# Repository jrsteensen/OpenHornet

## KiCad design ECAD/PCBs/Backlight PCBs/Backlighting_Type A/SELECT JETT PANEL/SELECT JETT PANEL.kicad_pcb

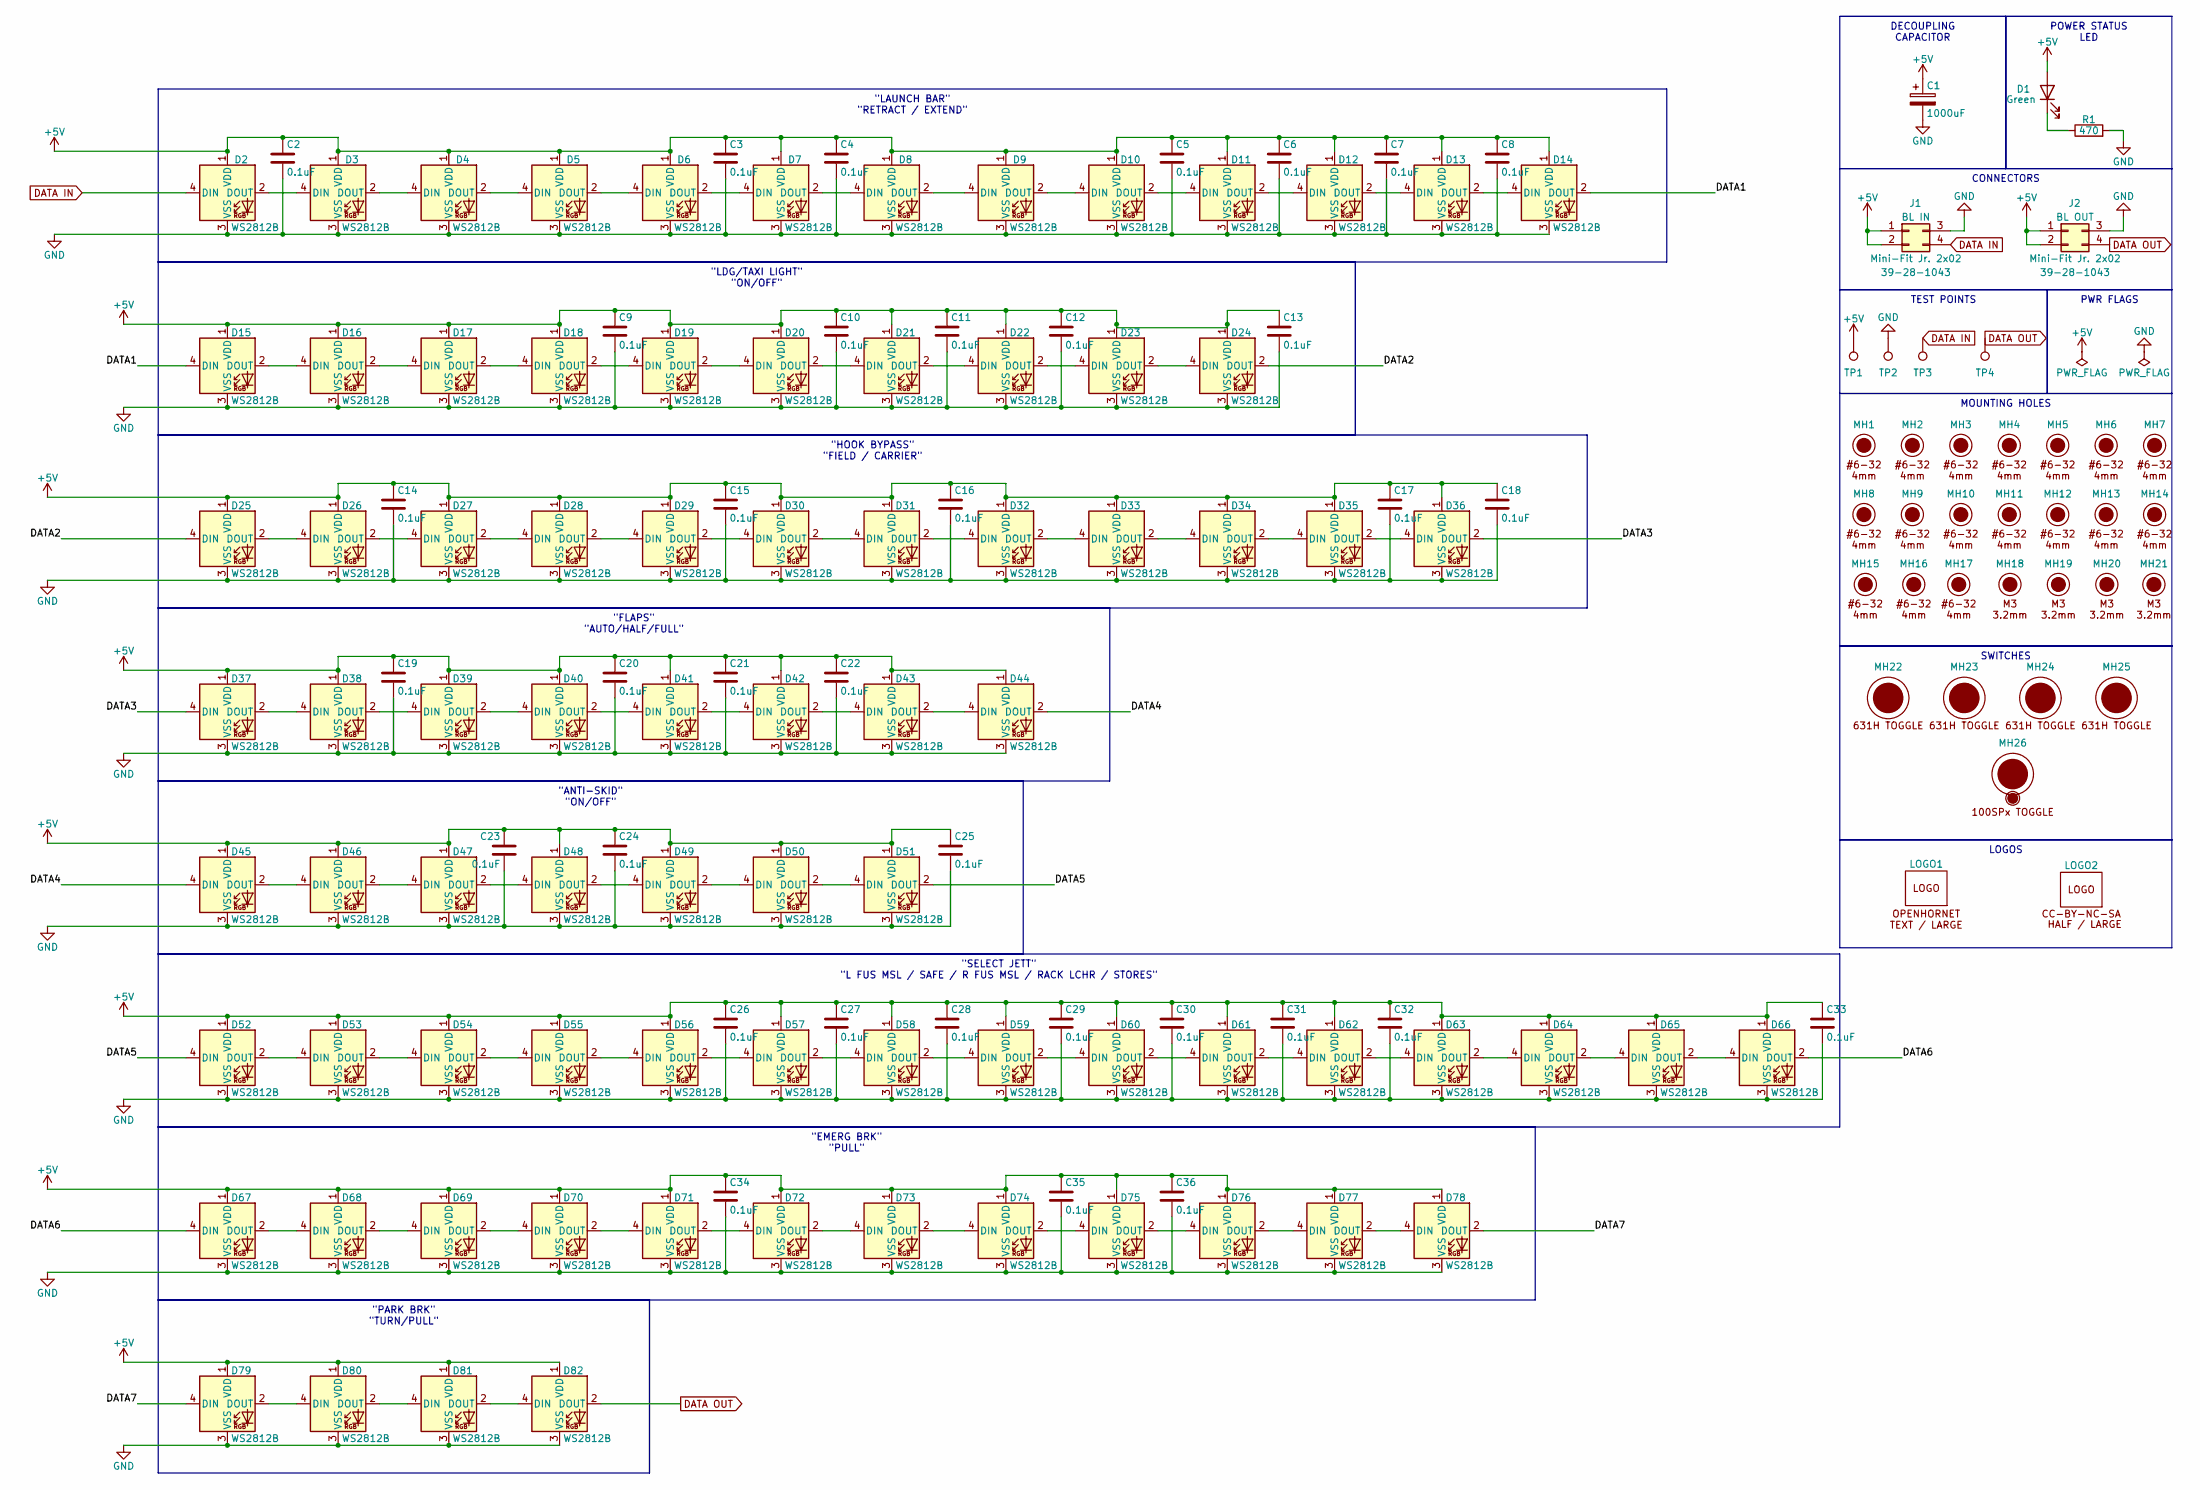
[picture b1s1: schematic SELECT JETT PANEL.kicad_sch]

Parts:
C1: 1000uF; CP_Elec_8x10; Manufacturer PN UWT0J102MNL1GS; LCSC C445083
C2, C3, C4, C5, C6, C7, C8, C9, C10, C11, C12, C13, C14, C15, C16, C17, C18, C19, C20, C21, C22, C23, C24, C25, C26, C27, C28, C29, C30, C31, C32, C33, C34, C35, C36: 0.1uF; C_0603_1608Metric; Manufacturer PN CC0603KRX7R9BB104; LCSC C14663
D1: Green; LED_D3.0mm; Manufacturer PN 151031VS06000
D2, D3, D4, D5, D6, D7, D8, D9, D10, D11, D12, D13, D14, D15, D16, D17, D18, D19, D20, D21, D22, D23, D24, D25, D26, D27, D28, D29, D30, D31, D32, D33, D34, D35, D36, D37, D38, D39, D40, D41, D42, D43, D44, D45, D46, D47, D48, D49, D50, D51, D52, D53, D54, D55, D56, D57, D58, D59, D60, D61, D62, D63, D64, D65, D66, D67, D68, D69, D70, D71, D72, D73, D74, D75, D76, D77, D78, D79, D80, D81, D82: WS2812B; LED_WS2812B_PLCC4_5.0x5.0mm_P3.2mm; Manufacturer PN WS2812B; LCSC C2761795
J1, J2: Mini-Fit Jr. 2x02; Molex_Mini-Fit_Jr_5566-04A_2x02_P4.20mm_Vertical; Manufacturer PN 39-28-1043; LCSC C293502
LOGO1: LOGO; LOGO_OH_Text_Large
LOGO2: LOGO; LOGO_CC-BY-NC-SA_Half_Large
MH1, MH2, MH3, MH4, MH5, MH6, MH7, MH8, MH9, MH10, MH11, MH12, MH13, MH14, MH15, MH16, MH17: 6x32 / 4mm; MountingHole_6-32_PHS
MH18, MH19, MH20, MH21: M3 / 3.2mm; MountingHole_3.2mm_M3_DIN965
MH22, MH23, MH24, MH25: Switch_631H; 631HX_Toggle_13mm_x_13mm; Manufacturer PN 631H
MH26: Switch_100SPx; 100SPX_Toggle_13mm_x_18mm
R1: 470; R_0603_1608Metric; Manufacturer PN 0603WAF4700T5E; LCSC C23179
TP1, TP2, TP3, TP4: TestPoint; TestPoint_THTPad_D1.5mm_Drill0.7mm

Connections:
+5V: C1.1, C2.1, C3.1, C4.1, C5.1, C6.1, C7.1, C8.1, C9.1, C10.1, C11.1, C12.1, C13.1, C14.1, C15.1, C16.1, C17.1, C18.1, C19.1, C20.1, C21.1, C22.1, C23.1, C24.1, C25.1, C26.1, C27.1, C28.1, C29.1, C30.1, C31.1, C32.1, C33.1, C34.1, C35.1, C36.1, D1.2 (A), D2.1 (VDD), D3.1 (VDD), D4.1 (VDD), D5.1 (VDD), D6.1 (VDD), D7.1 (VDD), D8.1 (VDD), D9.1 (VDD), D10.1 (VDD), D11.1 (VDD), D12.1 (VDD), D13.1 (VDD), D14.1 (VDD), D15.1 (VDD), D16.1 (VDD), D17.1 (VDD), D18.1 (VDD), D19.1 (VDD), D20.1 (VDD), D21.1 (VDD), D22.1 (VDD), D23.1 (VDD), D24.1 (VDD), D25.1 (VDD), D26.1 (VDD), D27.1 (VDD), D28.1 (VDD), D29.1 (VDD), D30.1 (VDD), D31.1 (VDD), D32.1 (VDD), D33.1 (VDD), D34.1 (VDD), D35.1 (VDD), D36.1 (VDD), D37.1 (VDD), D38.1 (VDD), D39.1 (VDD), D40.1 (VDD), D41.1 (VDD), D42.1 (VDD), D43.1 (VDD), D44.1 (VDD), D45.1 (VDD), D46.1 (VDD), D47.1 (VDD), D48.1 (VDD), D49.1 (VDD), D50.1 (VDD), D51.1 (VDD), D52.1 (VDD), D53.1 (VDD), D54.1 (VDD), D55.1 (VDD), D56.1 (VDD), D57.1 (VDD), D58.1 (VDD), D59.1 (VDD), D60.1 (VDD), D61.1 (VDD), D62.1 (VDD), D63.1 (VDD), D64.1 (VDD), D65.1 (VDD), D66.1 (VDD), D67.1 (VDD), D68.1 (VDD), D69.1 (VDD), D70.1 (VDD), D71.1 (VDD), D72.1 (VDD), D73.1 (VDD), D74.1 (VDD), D75.1 (VDD), D76.1 (VDD), D77.1 (VDD), D78.1 (VDD), D79.1 (VDD), D80.1 (VDD), D81.1 (VDD), D82.1 (VDD), J1.1, J1.2 (Pin_3), J2.1, J2.2 (Pin_3), TP1.1
/DATA1: D14.2 (DOUT), D15.4 (DIN)
/DATA2: D24.2 (DOUT), D25.4 (DIN)
/DATA3: D36.2 (DOUT), D37.4 (DIN)
/DATA4: D44.2 (DOUT), D45.4 (DIN)
/DATA5: D51.2 (DOUT), D52.4 (DIN)
/DATA6: D66.2 (DOUT), D67.4 (DIN)
/DATA7: D78.2 (DOUT), D79.4 (DIN)
DATA IN: D2.4 (DIN), J1.4, TP3.1
DATA OUT: D82.2 (DOUT), J2.4, TP4.1
GND: C1.2, C2.2, C3.2, C4.2, C5.2, C6.2, C7.2, C8.2, C9.2, C10.2, C11.2, C12.2, C13.2, C14.2, C15.2, C16.2, C17.2, C18.2, C19.2, C20.2, C21.2, C22.2, C23.2, C24.2, C25.2, C26.2, C27.2, C28.2, C29.2, C30.2, C31.2, C32.2, C33.2, C34.2, C35.2, C36.2, D2.3 (VSS), D3.3 (VSS), D4.3 (VSS), D5.3 (VSS), D6.3 (VSS), D7.3 (VSS), D8.3 (VSS), D9.3 (VSS), D10.3 (VSS), D11.3 (VSS), D12.3 (VSS), D13.3 (VSS), D14.3 (VSS), D15.3 (VSS), D16.3 (VSS), D17.3 (VSS), D18.3 (VSS), D19.3 (VSS), D20.3 (VSS), D21.3 (VSS), D22.3 (VSS), D23.3 (VSS), D24.3 (VSS), D25.3 (VSS), D26.3 (VSS), D27.3 (VSS), D28.3 (VSS), D29.3 (VSS), D30.3 (VSS), D31.3 (VSS), D32.3 (VSS), D33.3 (VSS), D34.3 (VSS), D35.3 (VSS), D36.3 (VSS), D37.3 (VSS), D38.3 (VSS), D39.3 (VSS), D40.3 (VSS), D41.3 (VSS), D42.3 (VSS), D43.3 (VSS), D44.3 (VSS), D45.3 (VSS), D46.3 (VSS), D47.3 (VSS), D48.3 (VSS), D49.3 (VSS), D50.3 (VSS), D51.3 (VSS), D52.3 (VSS), D53.3 (VSS), D54.3 (VSS), D55.3 (VSS), D56.3 (VSS), D57.3 (VSS), D58.3 (VSS), D59.3 (VSS), D60.3 (VSS), D61.3 (VSS), D62.3 (VSS), D63.3 (VSS), D64.3 (VSS), D65.3 (VSS), D66.3 (VSS), D67.3 (VSS), D68.3 (VSS), D69.3 (VSS), D70.3 (VSS), D71.3 (VSS), D72.3 (VSS), D73.3 (VSS), D74.3 (VSS), D75.3 (VSS), D76.3 (VSS), D77.3 (VSS), D78.3 (VSS), D79.3 (VSS), D80.3 (VSS), D81.3 (VSS), D82.3 (VSS), J1.3 (Pin_2), J2.3 (Pin_2), R1.2, TP2.1
unnamed: D1.1 (K), R1.1
unnamed: D2.2 (DOUT), D3.4 (DIN)
unnamed: D3.2 (DOUT), D4.4 (DIN)
unnamed: D4.2 (DOUT), D5.4 (DIN)
unnamed: D5.2 (DOUT), D6.4 (DIN)
unnamed: D6.2 (DOUT), D7.4 (DIN)
unnamed: D7.2 (DOUT), D8.4 (DIN)
unnamed: D8.2 (DOUT), D9.4 (DIN)
unnamed: D9.2 (DOUT), D10.4 (DIN)
unnamed: D10.2 (DOUT), D11.4 (DIN)
unnamed: D11.2 (DOUT), D12.4 (DIN)
unnamed: D12.2 (DOUT), D13.4 (DIN)
unnamed: D13.2 (DOUT), D14.4 (DIN)
unnamed: D15.2 (DOUT), D16.4 (DIN)
unnamed: D16.2 (DOUT), D17.4 (DIN)
unnamed: D17.2 (DOUT), D18.4 (DIN)
unnamed: D18.2 (DOUT), D19.4 (DIN)
unnamed: D19.2 (DOUT), D20.4 (DIN)
unnamed: D20.2 (DOUT), D21.4 (DIN)
unnamed: D21.2 (DOUT), D22.4 (DIN)
unnamed: D22.2 (DOUT), D23.4 (DIN)
unnamed: D23.2 (DOUT), D24.4 (DIN)
unnamed: D25.2 (DOUT), D26.4 (DIN)
unnamed: D26.2 (DOUT), D27.4 (DIN)
unnamed: D27.2 (DOUT), D28.4 (DIN)
unnamed: D28.2 (DOUT), D29.4 (DIN)
unnamed: D29.2 (DOUT), D30.4 (DIN)
unnamed: D30.2 (DOUT), D31.4 (DIN)
unnamed: D31.2 (DOUT), D32.4 (DIN)
unnamed: D32.2 (DOUT), D33.4 (DIN)
unnamed: D33.2 (DOUT), D34.4 (DIN)
unnamed: D34.2 (DOUT), D35.4 (DIN)
unnamed: D35.2 (DOUT), D36.4 (DIN)
unnamed: D37.2 (DOUT), D38.4 (DIN)
unnamed: D38.2 (DOUT), D39.4 (DIN)
unnamed: D39.2 (DOUT), D40.4 (DIN)
unnamed: D40.2 (DOUT), D41.4 (DIN)
unnamed: D41.2 (DOUT), D42.4 (DIN)
unnamed: D42.2 (DOUT), D43.4 (DIN)
unnamed: D43.2 (DOUT), D44.4 (DIN)
unnamed: D45.2 (DOUT), D46.4 (DIN)
unnamed: D46.2 (DOUT), D47.4 (DIN)
unnamed: D47.2 (DOUT), D48.4 (DIN)
unnamed: D48.2 (DOUT), D49.4 (DIN)
unnamed: D49.2 (DOUT), D50.4 (DIN)
unnamed: D50.2 (DOUT), D51.4 (DIN)
unnamed: D52.2 (DOUT), D53.4 (DIN)
unnamed: D53.2 (DOUT), D54.4 (DIN)
unnamed: D54.2 (DOUT), D55.4 (DIN)
unnamed: D55.2 (DOUT), D56.4 (DIN)
unnamed: D56.2 (DOUT), D57.4 (DIN)
unnamed: D57.2 (DOUT), D58.4 (DIN)
unnamed: D58.2 (DOUT), D59.4 (DIN)
unnamed: D59.2 (DOUT), D60.4 (DIN)
unnamed: D60.2 (DOUT), D61.4 (DIN)
unnamed: D61.2 (DOUT), D62.4 (DIN)
unnamed: D62.2 (DOUT), D63.4 (DIN)
unnamed: D63.2 (DOUT), D64.4 (DIN)
unnamed: D64.2 (DOUT), D65.4 (DIN)
unnamed: D65.2 (DOUT), D66.4 (DIN)
unnamed: D67.2 (DOUT), D68.4 (DIN)
unnamed: D68.2 (DOUT), D69.4 (DIN)
unnamed: D69.2 (DOUT), D70.4 (DIN)
unnamed: D70.2 (DOUT), D71.4 (DIN)
unnamed: D71.2 (DOUT), D72.4 (DIN)
unnamed: D72.2 (DOUT), D73.4 (DIN)
unnamed: D73.2 (DOUT), D74.4 (DIN)
unnamed: D74.2 (DOUT), D75.4 (DIN)
unnamed: D75.2 (DOUT), D76.4 (DIN)
unnamed: D76.2 (DOUT), D77.4 (DIN)
unnamed: D77.2 (DOUT), D78.4 (DIN)
unnamed: D79.2 (DOUT), D80.4 (DIN)
unnamed: D80.2 (DOUT), D81.4 (DIN)
unnamed: D81.2 (DOUT), D82.4 (DIN)

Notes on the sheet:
PWR FLAGS
LOGOS
"FLAPS" "AUTO/HALF/FULL"
POWER STATUS LED
"EMERG BRK" "PULL"
"ANTI-SKID" "ON/OFF"
CONNECTORS
"LDG/TAXI LIGHT" "ON/OFF"
"SELECT JETT" "L FUS MSL / SAFE / R FUS MSL / RACK LCHR / STORES"
"PARK BRK" "TURN/PULL"
DECOUPLING CAPACITOR
"LAUNCH BAR" "RETRACT / EXTEND"
SWITCHES
"HOOK BYPASS" "FIELD / CARRIER"
MOUNTING HOLES
TEST POINTS

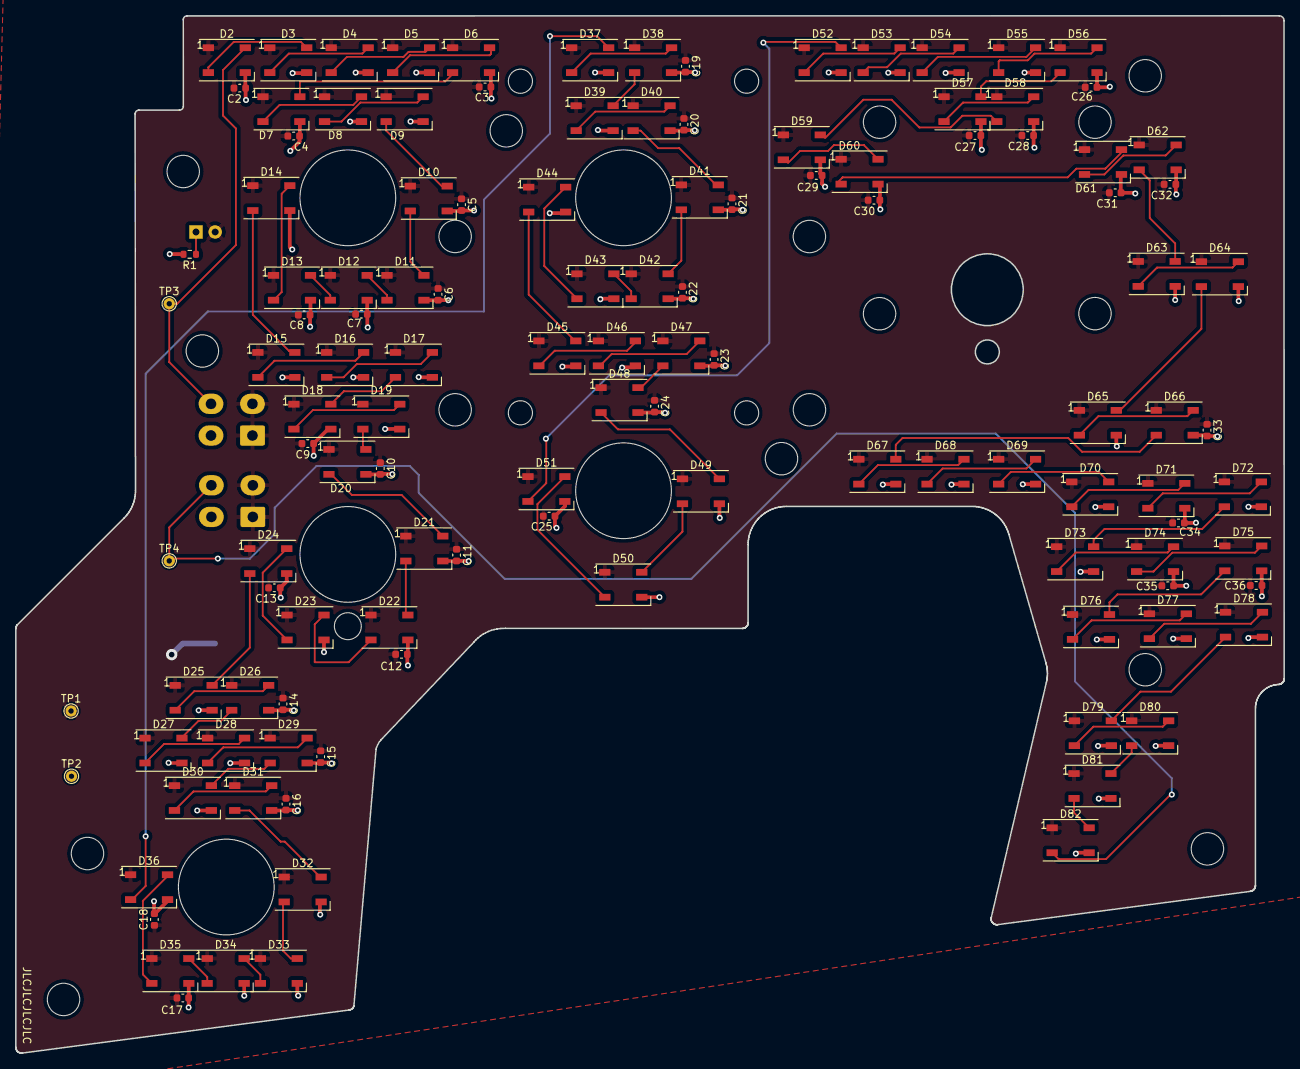
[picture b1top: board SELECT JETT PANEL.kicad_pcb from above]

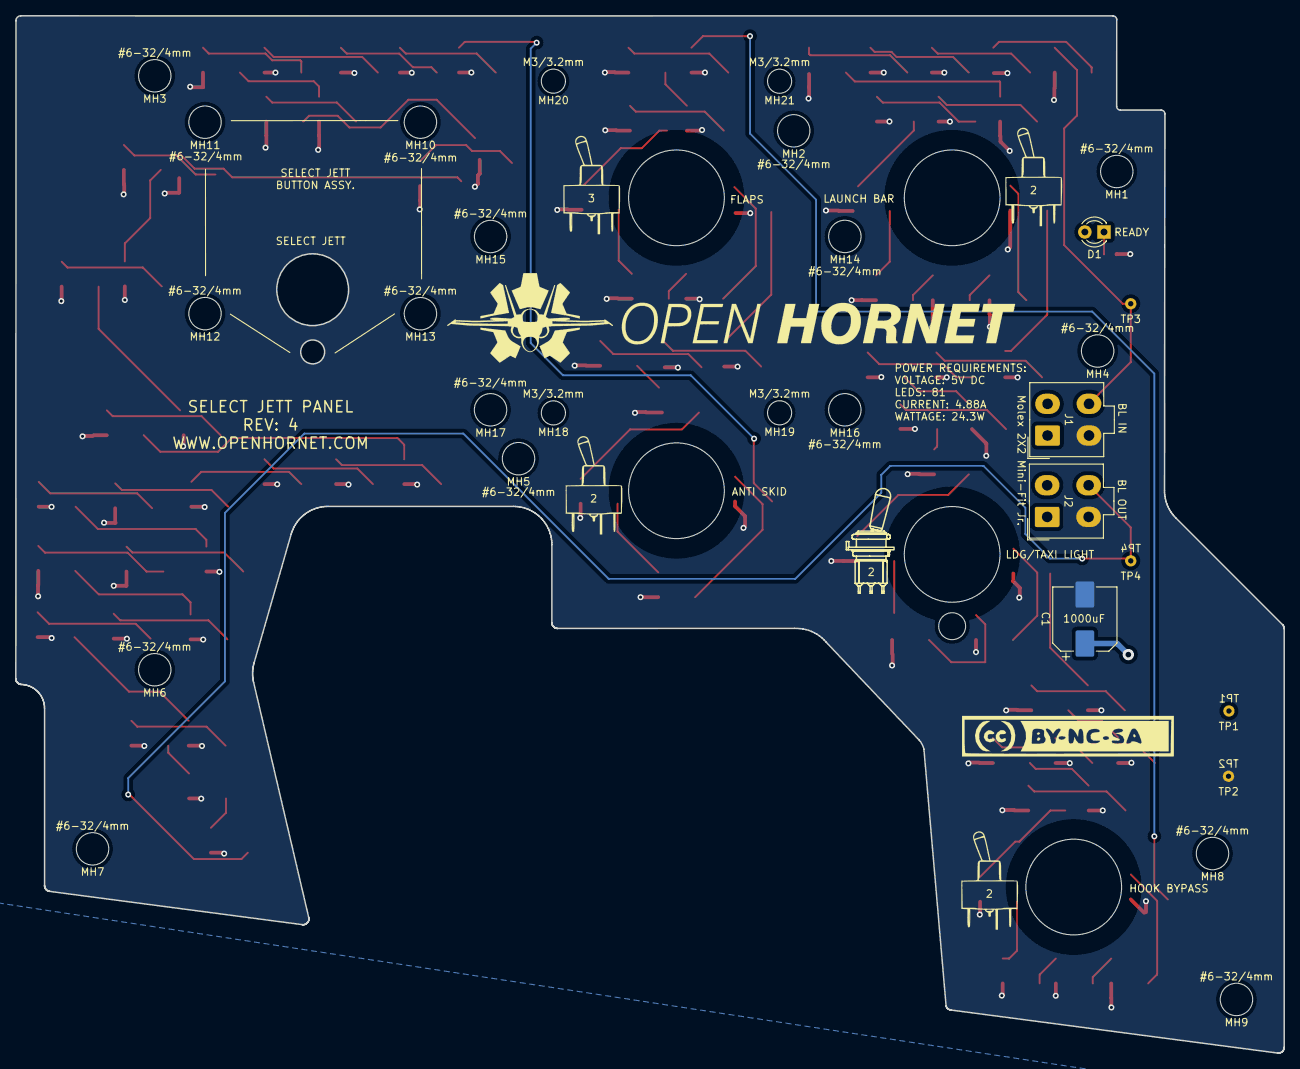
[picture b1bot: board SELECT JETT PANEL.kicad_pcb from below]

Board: 2 copper layers, 168.3 x 137.6 mm, 158 parts (32 on the bottom side), 85 nets.

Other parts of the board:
LOGO3, LOGO5, LOGO6: LOGO; 631H2_Toggle_Silkscreen
LOGO4: LOGO; 631H3_Toggle_Silkscreen
LOGO7: LOGO; 100SP1_Toggle_Silkscreen

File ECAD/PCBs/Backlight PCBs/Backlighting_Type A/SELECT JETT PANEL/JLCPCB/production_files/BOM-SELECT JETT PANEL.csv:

Comment,Designator,Footprint,LCSC
0.1uF,"C10,C11,C12,C13,C14,C15,C16,C17,C18,C19,C2,C20,C21,C22,C23,C24,C25,C26,C27,C28,C29,C3,C30,C31,C32,C33,C34,C35,C36,C4,C5,C6,C7,C8,C9",C_0603_1608Metric,C14663
470,R1,R_0603_1608Metric,C23179
WS2812B,"D10,D11,D12,D13,D14,D15,D16,D17,D18,D19,D2,D20,D21,D22,D23,D24,D25,D26,D27,D28,D29,D3,D30,D31,D32,D33,D34,D35,D36,D37,D38,D39,D4,D40,D41,D42,D43,D44,D45,D46,D47,D48,D49,D5,D50,D51,D52,D53,D54,D55,D56,D57,D58,D59,D6,D60,D61,D62,D63,D64,D65,D66,D67,D68,D69,D7,D70,D71,D72,D73,D74,D75,D76,D77,D78,D79,D8,D80,D81,D82,D9",LED_WS2812B_PLCC4_5.0x5.0mm_P3.2mm,C2761795
Mini-Fit Jr. 2x02,"J1,J2",Molex_Mini-Fit_Jr_5566-04A_2x02_P4.20mm_Vertical,C293502
1000uF,C1,CP_Elec_8x10,C445083
Green,D1,LED_D3.0mm,

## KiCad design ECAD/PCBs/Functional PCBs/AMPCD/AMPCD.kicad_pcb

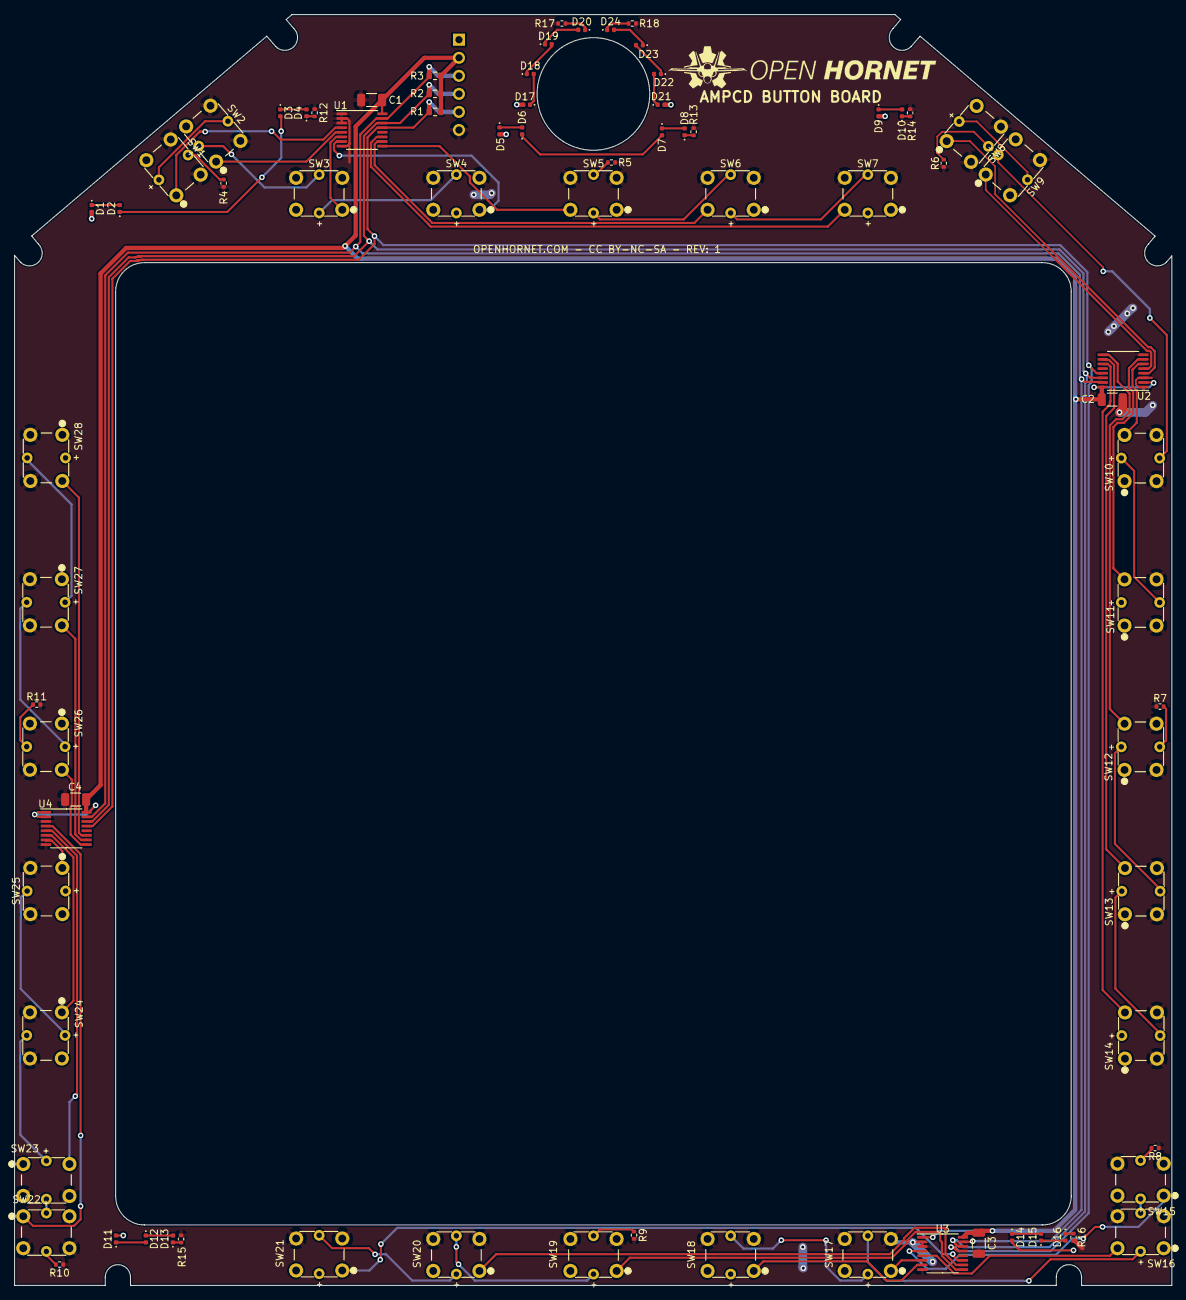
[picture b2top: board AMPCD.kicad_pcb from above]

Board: 2 copper layers, 162.9 x 178.9 mm, 79 parts (1 on the bottom side), 72 nets.

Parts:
C1, C2, C3, C4: 47uF; C_1206_3216Metric
D1, D2, D3, D4, D5, D6, D7, D8, D9, D10, D11, D12, D13, D14, D15, D16, D17, D18, D19, D20, D21, D22, D23, D24: LED; LED_0402_1005Metric
J1: Conn_01x06; PinHeader_1x06_P2.54mm_Horizontal
R1, R2, R3: 10K; R_0603_1608Metric
R4, R6, R8, R10, R12, R13, R17, R18: 33; R_0402_1005Metric
R5, R7, R9, R11, R15, R16: 150; R_0402_1005Metric
R14: 270; R_0402_1005Metric
SW1, SW2, SW3, SW4, SW5, SW6, SW7, SW8, SW9, SW10, SW11, SW12, SW13, SW14, SW15, SW16, SW17, SW18, SW19, SW20, SW21, SW22, SW23, SW24, SW25, SW26, SW27, SW28: TL1240GQ_old
U1, U2, U3, U4: TCA9554PWR; TSSOP-16_4.4x5mm_P0.65mm

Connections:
+5V: C1.1, C2.1, C3.1, C4.1, J1.2, R1.1, R2.1, R3.1, U1.16, U2.2, U2.16, U3.1, U3.16, U4.1, U4.2, U4.16
/U1P3: SW4.1, U1.7
/U1P4: SW5.1, U1.9
/U1P5: SW6.1, U1.10
/U1P6: SW7.1, U1.11
/U2P0: SW8.1, U2.4
/U2P1: SW9.1, U2.5
/U2P4: SW12.1, U2.9
/U2P5: SW13.1, U2.10
/U2P6: SW14.1, U2.11
/U3P4: SW19.1, U3.9
/U3P5: SW20.1, U3.10
/U3P6: SW21.1, U3.11
/U4P0: SW22.1, U4.4
/U4P1: SW23.1, U4.5
GND: C1.2, C2.2, C3.2, C4.2, J1.6, R4.1, R5.1, R6.1, R7.1, R8.1, R9.1, R10.1, R11.1, R12.2, R13.2, R14.2, R15.2, R16.2, R17.2, R18.2, SW1.2, SW2.2, SW3.2, SW4.2, SW5.2, SW6.2, SW7.2, SW8.2, SW9.2, SW10.2, SW11.2, SW12.2, SW13.2, SW14.2, SW15.2, SW16.2, SW17.2, SW18.2, SW19.2, SW20.2, SW21.2, SW22.2, SW23.2, SW24.2, SW25.2, SW26.2, SW27.2, SW28.2, U1.1, U1.2, U1.3, U1.8, U2.1, U2.3, U2.8, U3.2, U3.3, U3.8, U4.3, U4.8
IRQ: J1.5, R1.2, U1.13, U2.13, U3.13, U4.13
unnamed: D1.1, D2.2
unnamed: D2.1, D3.2
unnamed: D3.1, D4.2
unnamed: D4.1, R12.1
unnamed: D5.1, D6.2
unnamed: D6.1, D7.2
unnamed: D7.1, D8.2
unnamed: D8.1, R13.1
unnamed: D10.1, R14.1
unnamed: D9.1, D10.2
unnamed: D11.1, D12.2
unnamed: D12.1, D13.2
unnamed: D13.1, R15.1
unnamed: D14.1, D15.2
unnamed: D15.1, D16.2
unnamed: D16.1, R16.1
unnamed: D17.1, D18.2
unnamed: D18.1, D19.2
unnamed: D19.1, D20.2
unnamed: D20.1, R17.1
unnamed: D21.1, D22.2
unnamed: D22.1, D23.2
unnamed: D23.1, D24.2
unnamed: D24.1, R18.1
unnamed: R4.2, SW1.3
unnamed: R5.2, SW5.3
unnamed: R6.2, SW8.3
unnamed: R7.2, SW12.3
unnamed: R8.2, SW15.3
unnamed: R9.2, SW19.3
unnamed: R10.2, SW22.3
unnamed: R11.2, SW26.3
unnamed: SW1.4, SW2.3
unnamed: SW2.4, SW3.3
unnamed: SW3.4, SW4.3
unnamed: SW5.4, SW6.3
unnamed: SW6.4, SW7.3
unnamed: SW8.4, SW9.3
unnamed: SW9.4, SW10.3
unnamed: SW10.4, SW11.3
unnamed: SW12.4, SW13.3
unnamed: SW13.4, SW14.3
unnamed: SW15.4, SW16.3
unnamed: SW16.4, SW17.3
unnamed: SW17.4, SW18.3
unnamed: SW19.4, SW20.3
unnamed: SW20.4, SW21.3
unnamed: SW22.4, SW23.3
unnamed: SW23.4, SW24.3
unnamed: SW24.4, SW25.3
unnamed: SW26.4, SW27.3
unnamed: SW27.4, SW28.3
SCL: J1.4, R2.2, U1.14, U2.14, U3.14, U4.14
SDA: J1.3, R3.2, U1.15, U2.15, U3.15, U4.15
VCC: D1.2, D5.2, D9.2, D11.2, D14.2, D17.2, D21.2, J1.1, SW4.4, SW7.4, SW11.4, SW14.4, SW18.4, SW21.4, SW25.4, SW28.4

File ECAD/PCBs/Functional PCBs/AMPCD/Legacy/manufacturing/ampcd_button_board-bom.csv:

Comment,Designator,Footprint,LCSC
"47uF","C1,C2,C3,C4","Capacitor_SMD:C_1206_3216Metric","C96123"
"LED","D1,D2,D3,D4,D5,D6,D7,D8,D9,D10,D11,D12,D13,D14,D15,D16,D17,D18,D19,D20,D21,D22,D23,D24","LED_SMD:LED_0402_1005Metric","C130723"
"Conn_01x06","J1","Connector_PinHeader_2.54mm:PinHeader_1x06_P2.54mm_Horizontal",""
"33","R4,R6,R8,R10,R12,R13,R17,R18","Resistor_SMD:R_0402_1005Metric","C25105"
"270","R14","Resistor_SMD:R_0402_1005Metric","C25099"
"150","R5,R7,R9,R11,R15,R16","Resistor_SMD:R_0402_1005Metric","C25082"
"10K","R1,R2,R3","Resistor_SMD:R_0603_1608Metric","C25804"
"TL1240GQ","SW1,SW2,SW3,SW4,SW5,SW6,SW7,SW8,SW9,SW10,SW11,SW12,SW13,SW14,SW15,SW16,SW17,SW18,SW19,SW20,SW21,SW22,SW23,SW24,SW25,SW26,SW27,SW28","KiCAD Libraries:TL1240GQ",""
"TCA9554PWR","U1,U2,U3,U4","Package_SO:TSSOP-16_4.4x5mm_P0.65mm","C477924"

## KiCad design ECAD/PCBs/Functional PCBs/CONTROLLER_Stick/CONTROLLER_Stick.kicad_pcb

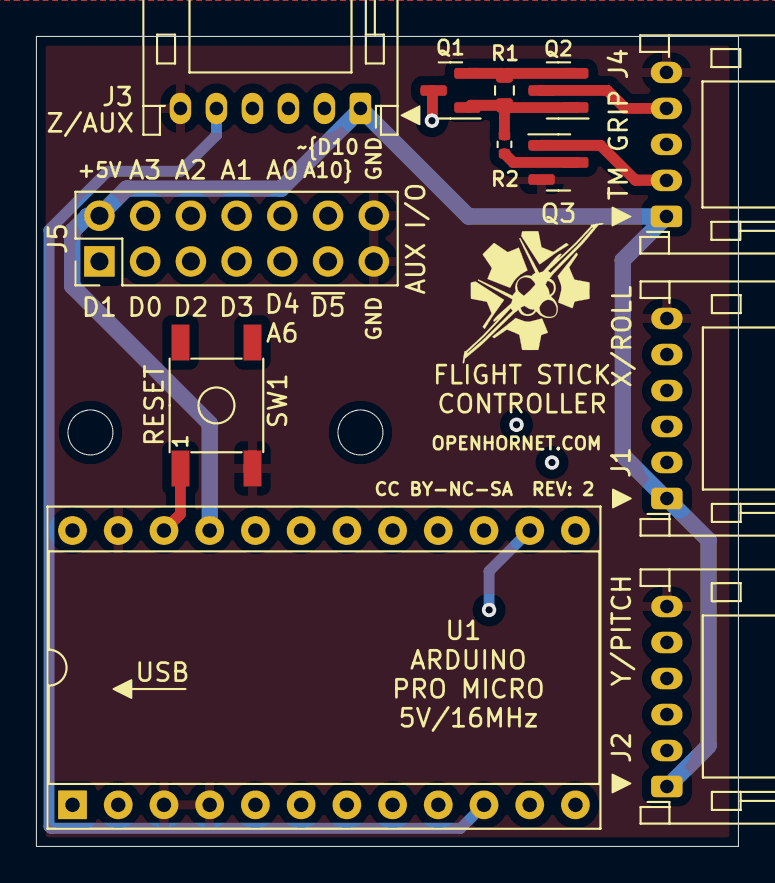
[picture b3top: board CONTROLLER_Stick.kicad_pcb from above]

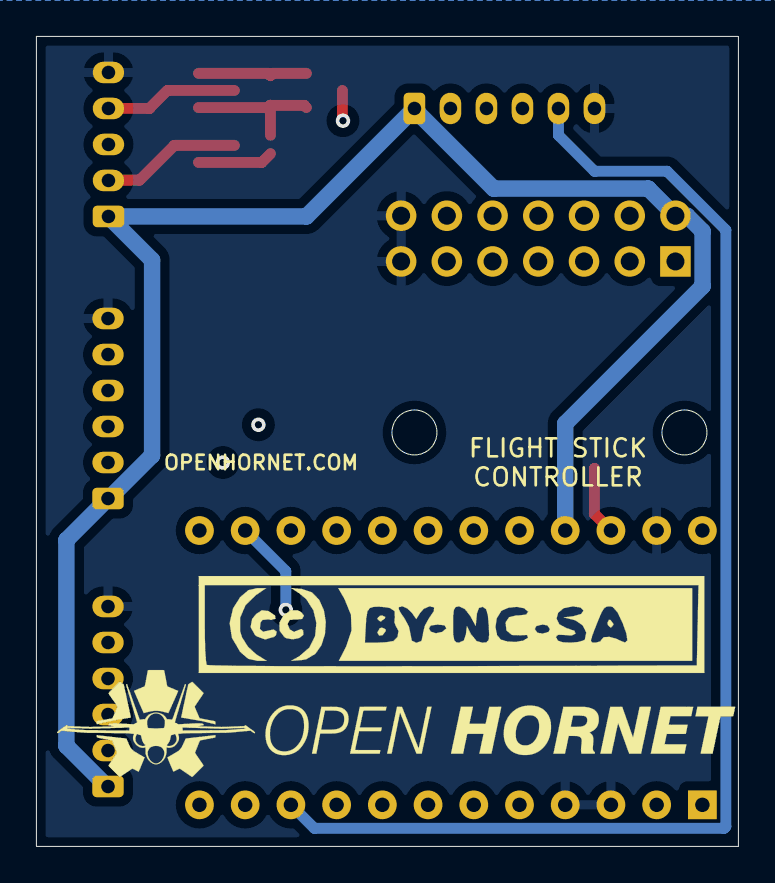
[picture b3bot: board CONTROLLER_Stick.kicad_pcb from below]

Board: 4 copper layers, 39.0 x 45.0 mm, 17 parts (2 on the bottom side), 25 nets.

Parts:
H1, H2: MountingHole; MountingHole_2.5mm
J1: X/ROLL; JST_PH_S6B-PH-K_1x06_P2.00mm_Horizontal
J2: Y/PITCH; JST_PH_S6B-PH-K_1x06_P2.00mm_Horizontal
J3: Z/AUX; JST_PH_S6B-PH-K_1x06_P2.00mm_Horizontal
J4: TM GRIP; JST_PH_S5B-PH-K_1x05_P2.00mm_Horizontal
J5: AUX I/O; PinHeader_2x07_P2.54mm_Vertical
LOGO1: OpenHornetLogoSmall; OH_LOGO_37.7mm_5.9mm
LOGO2: OpenHornetLogoSmall; CC-BY-NC-SA-Small
LOGO3: OpenHornetLogoSmall; OH_LOGO_ONLY_11x6mm
Q1, Q2: IRLML6402TRPBF; SOT-23
Q3: 2N7002; SOT-23
R1: 10k; R_0603_1608Metric
R2: 33; R_0402_1005Metric
SW1: RESET; SMD-SW-4_5.1x5.1
U1: ProMicro; DIP-24_W15.24mm_Socket

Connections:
+5V: J1.1, J2.1, J3.1, J4.1, J5.2, U1.21
/A0: J5.10, U1.17
/A1: J5.8, U1.18
/A2: J5.6, U1.19
/A3: J5.4, U1.20
/CSg: J4.2, Q3.1, U1.9
/CSx: J1.5, U1.12
/CSy: J2.5, U1.11
/CSz: J3.5, U1.10
/D0: J5.3, U1.2
/D1: J5.1, U1.1
/D2: J5.5, U1.5
/D4A6: J5.9, U1.7
/MISO: J1.2, J2.2, J3.2, Q1.3, U1.15
/MISOg: J4.4, Q2.3
/MOSI: J1.3, J2.3, J3.3, U1.14
/RST: SW1.1, U1.22
/SCK: J1.4, J2.4, J3.4, J4.3, U1.16
/~D3: J5.7, U1.6
/~D5: J5.11, U1.8
/~D10A10: J5.12, U1.13
GND: J1.6, J2.6, J3.6, J4.5, J5.13, J5.14, Q3.2, SW1.3, U1.3, U1.4, U1.23
unnamed: Q1.1, Q2.1, R1.2, R2.1
unnamed: Q1.2, Q2.2, R1.1
unnamed: Q3.3, R2.2

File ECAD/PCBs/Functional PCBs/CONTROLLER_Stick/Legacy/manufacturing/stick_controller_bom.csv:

Comment,Designator,Footprint,LCSC
"MountingHole","H1,H2","MountingHole:MountingHole_2.5mm",""
"X/ROLL","J1","Connector_JST:JST_PH_S6B-PH-K_1x06_P2.00mm_Horizontal","C265105"
"Y/PITCH","J2","Connector_JST:JST_PH_S6B-PH-K_1x06_P2.00mm_Horizontal","C265105"
"Z/AUX","J3","Connector_JST:JST_PH_S6B-PH-K_1x06_P2.00mm_Horizontal","C265105"
"TM GRIP","J4","Connector_JST:JST_PH_S5B-PH-K_1x05_P2.00mm_Horizontal","C157923"
"AUX I/O","J5","Connector_PinHeader_2.54mm:PinHeader_2x07_P2.54mm_Vertical",""
"OpenHornetLogoSmall","LOGO1","KiCAD Libraries:OH_LOGO_37.7mm_5.9mm",""
"OpenHornetLogoSmall","LOGO2","KiCAD Libraries:CC-BY-NC-SA-Small",""
"OpenHornetLogoSmall","LOGO3","KiCAD Libraries:OH_LOGO_ONLY_11x6mm",""
"IRLML6402TRPBF","Q1,Q2","Package_TO_SOT_SMD:SOT-23","C2593"
"2N7002","Q3","Package_TO_SOT_SMD:SOT-23","C8545"
"10k","R1","Resistor_SMD:R_0603_1608Metric","C25804"
"33","R2","Resistor_SMD:R_0402_1005Metric","C25105"
"RESET","SW1","KiCAD Libraries:SMD-SW-4_5.1x5.1","C318884"
"ProMicro","U1","Package_DIP:DIP-24_W15.24mm_Socket","C72120"

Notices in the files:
ECAD/PCBs/Backlight PCBs/Backlighting_Type A/SELECT JETT PANEL/SELECT JETT PANEL.kicad_pcb:
License:  CC BY-NC-SA
ECAD/PCBs/Functional PCBs/AMPCD/AMPCD.kicad_pcb:
OPENHORNET.COM - CC BY-NC-SA
OPENHORNET.COM - CC BY-NC-SA - REV: 1
ECAD/PCBs/Functional PCBs/CONTROLLER_Stick/CONTROLLER_Stick.kicad_pcb:
CC BY-NC-SA  REV: 2
parts and their libraries:
https://creativecommons.org/licenses/by-nc-sa/4.0
